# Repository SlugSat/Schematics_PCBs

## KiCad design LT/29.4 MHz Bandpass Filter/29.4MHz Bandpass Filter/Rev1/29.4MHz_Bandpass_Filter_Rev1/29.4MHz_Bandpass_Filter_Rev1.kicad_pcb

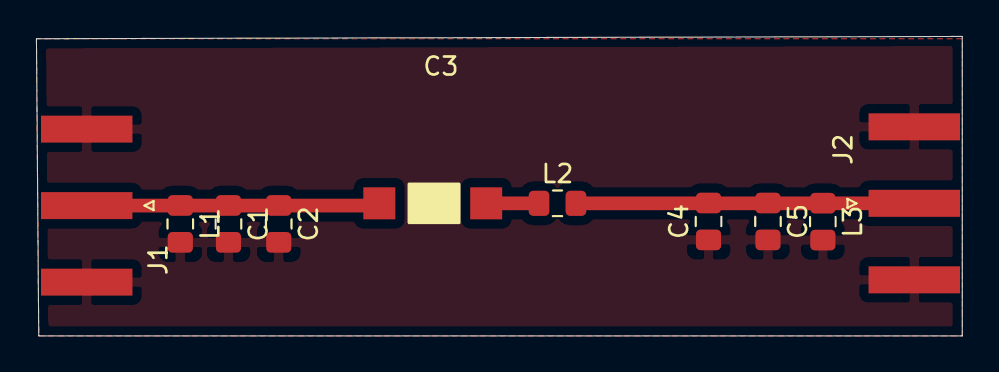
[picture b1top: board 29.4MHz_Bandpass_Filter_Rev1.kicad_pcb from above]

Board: 2 copper layers, 51.4 x 16.6 mm, 10 parts (0 on the bottom side), 4 nets.

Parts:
C1, C2, C4, C5: 1.2nF; C_0805_2012Metric_Pad1.15x1.40mm_HandSolder
C3: C_Variable; Variable Capacitor
J1, J2: Conn_Coaxial; SMA_Amphenol_132289_EdgeMount
L1, L3: 12nH; L_0805_2012Metric_Pad1.15x1.40mm_HandSolder
L2: 5.6uH; L_0805_2012Metric_Pad1.15x1.40mm_HandSolder

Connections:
GND: C1.2, C2.2, C4.1, C5.2, J1.2, J2.2, L1.2, L3.2
unnamed: C1.1, C2.1, C3.2, J1.1, L1.1
unnamed: C3.1, L2.1
unnamed: C4.2, C5.1, J2.1, L2.2, L3.1

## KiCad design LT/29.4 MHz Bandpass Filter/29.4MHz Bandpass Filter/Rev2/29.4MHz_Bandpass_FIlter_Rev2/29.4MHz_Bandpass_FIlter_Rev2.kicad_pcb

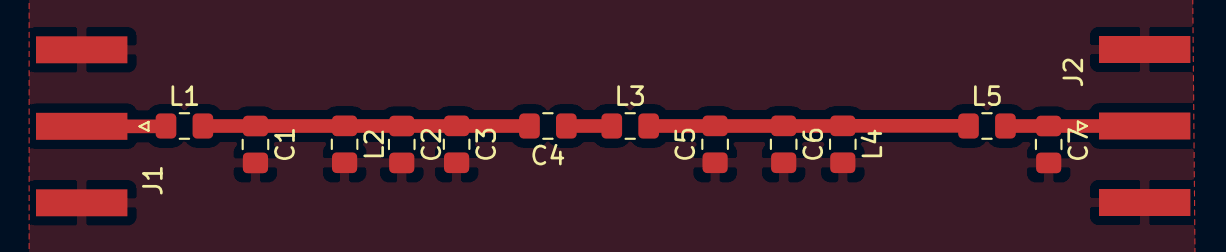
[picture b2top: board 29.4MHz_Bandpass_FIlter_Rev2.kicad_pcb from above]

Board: 2 copper layers, 14 parts (0 on the bottom side), 6 nets.

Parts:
C1, C7: 150pF; C_0805_2012Metric_Pad1.15x1.40mm_HandSolder
C2, C5: 1.5nF; C_0805_2012Metric_Pad1.15x1.40mm_HandSolder
C3, C6: 100pF; C_0805_2012Metric_Pad1.15x1.40mm_HandSolder
C4: 6.2pF; C_0805_2012Metric_Pad1.15x1.40mm_HandSolder
J1, J2: Conn_Coaxial; SMA_Amphenol_132289_EdgeMount
L1, L5: 82nH; L_0805_2012Metric_Pad1.15x1.40mm_HandSolder
L2: 18nH; L_0805_2012Metric_Pad1.15x1.40mm_HandSolder
L3: 4.7uH; L_0805_2012Metric_Pad1.15x1.40mm_HandSolder
L4: L; L_0805_2012Metric_Pad1.15x1.40mm_HandSolder

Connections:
GND: C1.2, C2.2, C3.2, C5.1, C6.2, C7.2, J1.2, J2.2, L2.2, L4.2
unnamed: C1.1, C2.1, C3.1, C4.2, L1.2, L2.1
unnamed: C4.1, L3.1
unnamed: C5.2, C6.1, L3.2, L4.1, L5.1
unnamed: C7.1, J2.1, L5.2
unnamed: J1.1, L1.1

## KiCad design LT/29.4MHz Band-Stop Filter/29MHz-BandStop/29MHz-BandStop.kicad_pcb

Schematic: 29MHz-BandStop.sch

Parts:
C1, C9: 8.2p; C_0805_2012Metric_Pad1.15x1.40mm_HandSolder
C2, C3, C6, C7, C10: C_Variable; CAP_trimmer_SGC3
C4, C8: 1.2n; C_0805_2012Metric_Pad1.15x1.40mm_HandSolder
C5: 15p; C_0805_2012Metric_Pad1.15x1.40mm_HandSolder
J1, J2: Conn_Coaxial; SMA_Molex_73251-1153_EdgeMount_Horizontal
L1, L9: 3.6u; C_0805_2012Metric_Pad1.15x1.40mm_HandSolder
L4, L8: 24n; C_0805_2012Metric_Pad1.15x1.40mm_HandSolder
L5: 2u; C_0805_2012Metric_Pad1.15x1.40mm_HandSolder
U1, U2, U3, U4, U5: LM3-IND; IND_trimmer_7M3

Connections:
GND: J1.2 (Ext), J2.2 (Ext), L1.2, L5.2, L9.2, U1.3, U3.3, U5.3
unnamed: C1.1, C2.1, C3.2, C4.1, J1.1 (In), L4.1, U2.1
unnamed: C1.2, C2.2, L1.1, U1.1
unnamed: C3.1, C4.2, C5.1, C6.1, C7.2, C8.1, L4.2, L8.1, U2.3, U4.1
unnamed: C5.2, C6.2, L5.1, U3.1
unnamed: C7.1, C8.2, C9.1, C10.1, J2.1 (In), L8.2, U4.3
unnamed: C9.2, C10.2, L9.1, U5.1

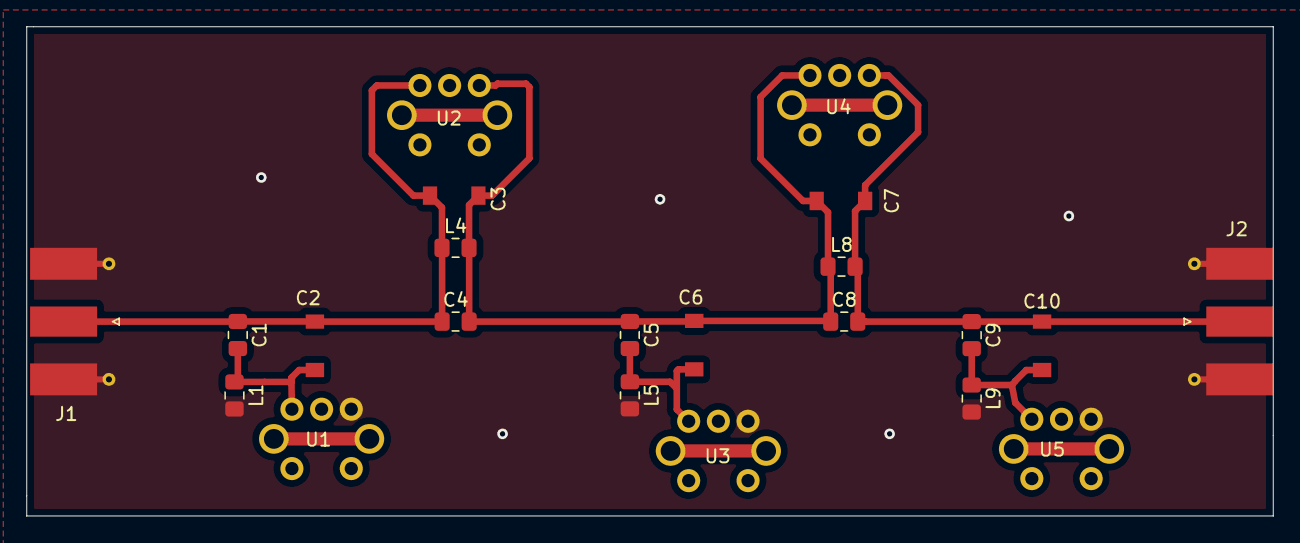
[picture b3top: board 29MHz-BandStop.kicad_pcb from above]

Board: 2 copper layers, 94.5 x 37.1 mm, 22 parts (0 on the bottom side), 7 nets.

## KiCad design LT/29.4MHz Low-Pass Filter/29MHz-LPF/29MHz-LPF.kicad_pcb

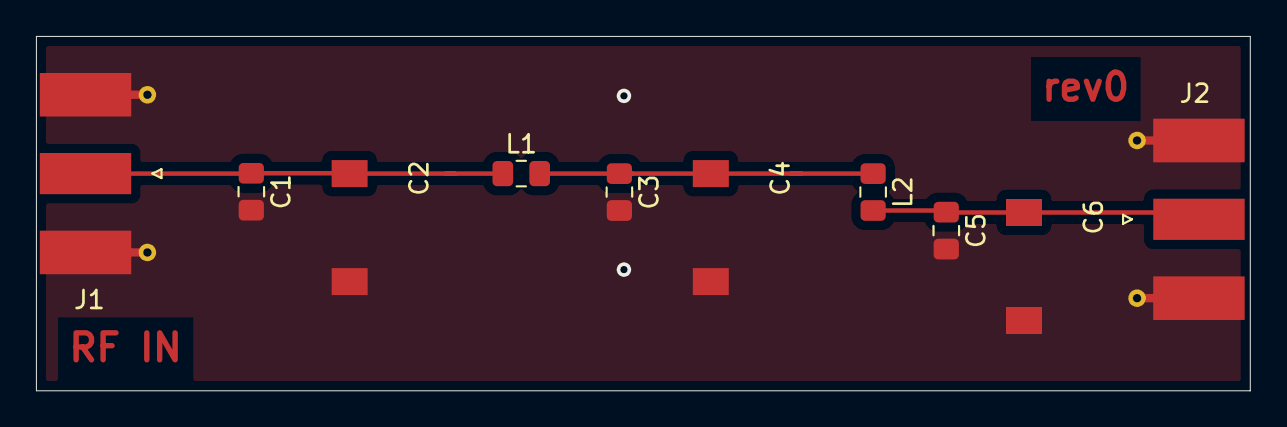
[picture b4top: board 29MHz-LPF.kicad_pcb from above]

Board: 2 copper layers, 67.4 x 19.7 mm, 10 parts (0 on the bottom side), 4 nets.

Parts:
C1, C5: 180p; C_0805_2012Metric_Pad1.15x1.40mm_HandSolder
C2, C4, C6: C_Variable; CAP_Trimmer_TZB4Z
C3: 270p; C_0805_2012Metric_Pad1.15x1.40mm_HandSolder
J1, J2: Conn_Coaxial; SMA_Molex_73251-1153_EdgeMount_Horizontal
L1, L2: 330n; L_0805_2012Metric_Pad1.15x1.40mm_HandSolder

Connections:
GND: C1.2, C2.2, C3.2, C4.2, C5.2, C6.2, J1.2, J2.2
unnamed: C1.1, C2.1, J1.1, L1.1
unnamed: C3.1, C4.1, L1.2, L2.1
unnamed: C5.1, C6.1, J2.1, L2.2

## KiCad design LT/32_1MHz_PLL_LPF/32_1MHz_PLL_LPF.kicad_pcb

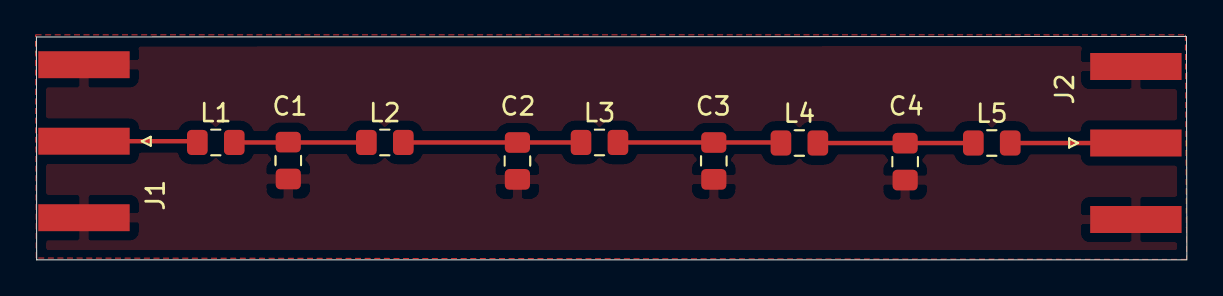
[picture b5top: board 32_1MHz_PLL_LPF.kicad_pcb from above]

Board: 2 copper layers, 63.9 x 12.4 mm, 11 parts (0 on the bottom side), 7 nets.

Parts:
C1, C4: 120pF; C_0805_2012Metric_Pad1.15x1.40mm_HandSolder
C2, C3: 200pF; C_0805_2012Metric_Pad1.15x1.40mm_HandSolder
J1, J2: Conn_Coaxial; SMA_Amphenol_132289_EdgeMount
L1, L5: Matching; L_0805_2012Metric_Pad1.15x1.40mm_HandSolder
L2: 360nH; L_0805_2012Metric_Pad1.15x1.40mm_HandSolder
L3: 390pF; L_0805_2012Metric_Pad1.15x1.40mm_HandSolder
L4: 360pF; L_0805_2012Metric_Pad1.15x1.40mm_HandSolder

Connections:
GND: C1.2, C2.2, C3.2, C4.2, J1.2, J2.2
unnamed: C1.1, L1.2, L2.1
unnamed: C2.1, L2.2, L3.1
unnamed: C3.1, L3.2, L4.1
unnamed: C4.1, L4.2, L5.1
unnamed: J1.1, L1.1
unnamed: J2.1, L5.2

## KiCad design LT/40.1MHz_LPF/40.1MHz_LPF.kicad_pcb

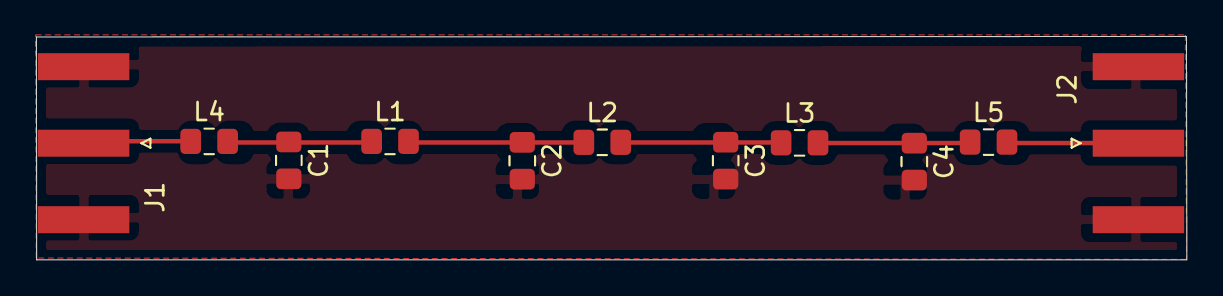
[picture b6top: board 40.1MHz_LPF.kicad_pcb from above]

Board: 2 copper layers, 63.9 x 12.4 mm, 11 parts (0 on the bottom side), 7 nets.

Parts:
C1: 91pF; C_0805_2012Metric_Pad1.15x1.40mm_HandSolder
C2, C3, C4: 160pF; C_0805_2012Metric_Pad1.15x1.40mm_HandSolder
J1, J2: Conn_Coaxial; SMA_Amphenol_132289_EdgeMount
L1, L3: 270nH; L_0805_2012Metric_Pad1.15x1.40mm_HandSolder
L2: 330nH; L_0805_2012Metric_Pad1.15x1.40mm_HandSolder
L4, L5: shorted; L_0805_2012Metric_Pad1.15x1.40mm_HandSolder

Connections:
GND: C1.2, C2.2, C3.2, C4.2, J1.2, J2.2
unnamed: C1.1, L1.1, L4.2
unnamed: C2.1, L1.2, L2.1
unnamed: C3.1, L2.2, L3.1
unnamed: C4.1, L3.2, L5.1
unnamed: J1.1, L4.1
unnamed: J2.1, L5.2

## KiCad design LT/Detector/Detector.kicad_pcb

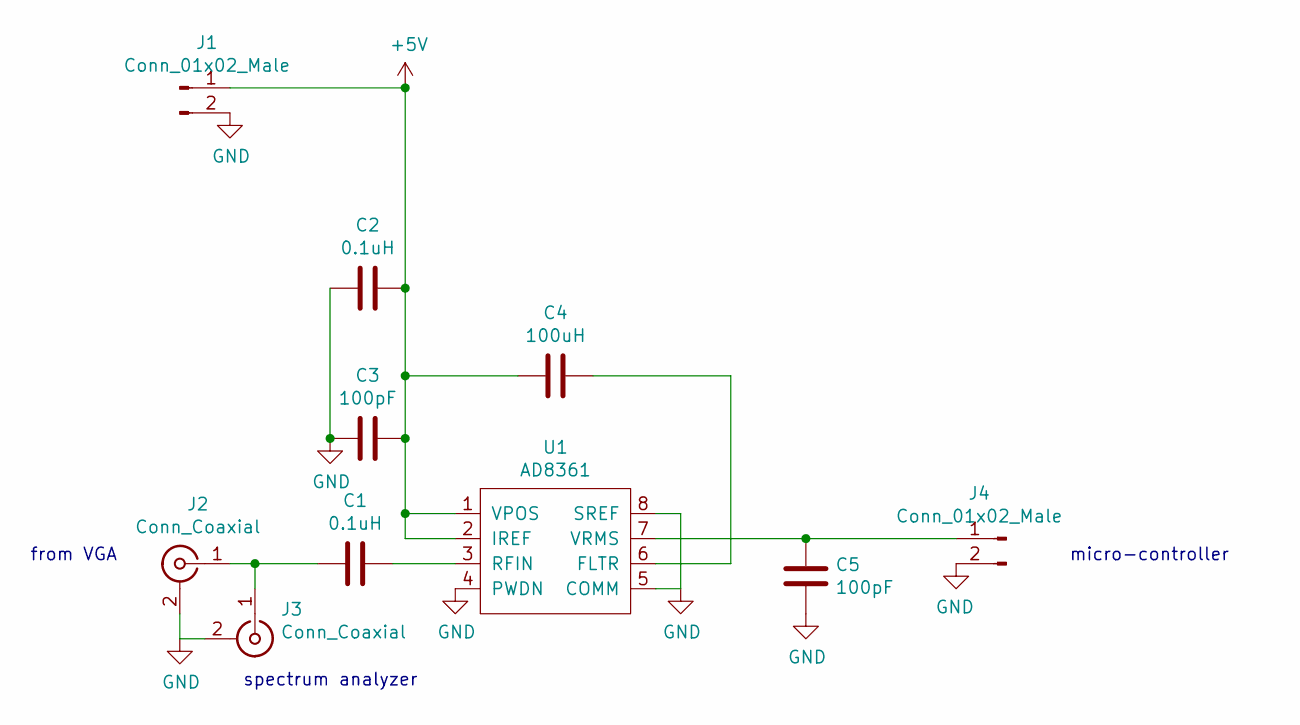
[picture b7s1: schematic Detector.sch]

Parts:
C1, C2: 0.1uH; C_0805_2012Metric_Pad1.15x1.40mm_HandSolder
C3, C5: 100pF; C_0805_2012Metric_Pad1.15x1.40mm_HandSolder
C4: 100uH; C_1206_3216Metric_Pad1.42x1.75mm_HandSolder
J1, J4: Conn_01x02_Male; PinHeader_1x02_P2.54mm_Vertical
J2, J3: Conn_Coaxial; SMA_Amphenol_132289_EdgeMount
U1: AD8361; MSOP-8_3x3mm_P0.65mm

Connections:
+5V: C2.1, C3.1, C4.2, J1.1, U1.1 (VPOS), U1.2 (IREF)
GND: C2.2, C3.2, C5.2, J1.2, J2.2 (Ext), J3.2 (Ext), J4.2, U1.4 (PWDN), U1.5 (COMM), U1.8 (SREF)
unnamed: C1.1, U1.3 (RFIN)
unnamed: C1.2, J2.1 (In), J3.1 (In)
unnamed: C4.1, U1.6 (FLTR)
unnamed: C5.1, J4.1, U1.7 (VRMS)

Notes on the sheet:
from VGA
spectrum analyzer
micro-controller

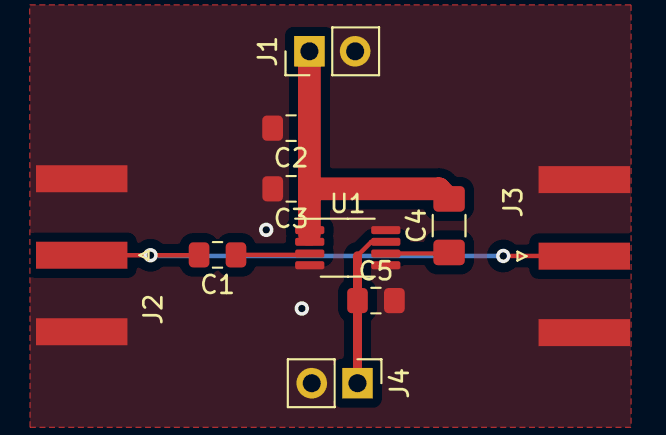
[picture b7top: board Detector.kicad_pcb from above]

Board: 2 copper layers, 10 parts (0 on the bottom side), 6 nets.

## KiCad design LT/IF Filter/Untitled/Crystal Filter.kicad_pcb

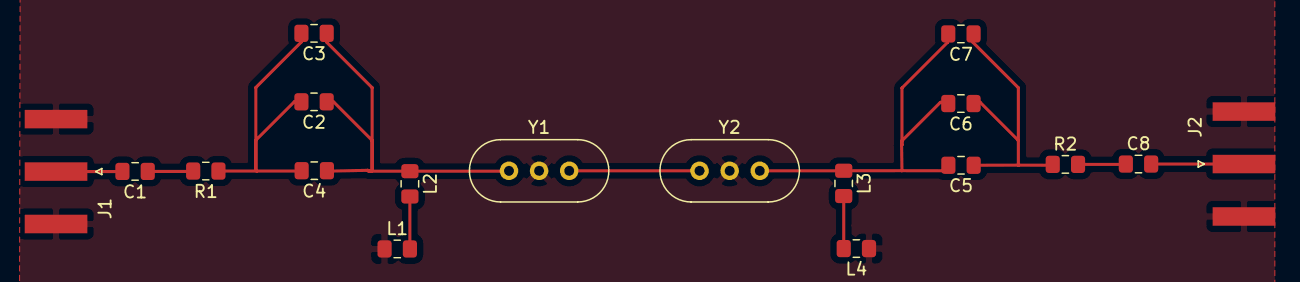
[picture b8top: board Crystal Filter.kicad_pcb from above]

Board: 2 copper layers, 18 parts (0 on the bottom side), 12 nets.

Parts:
C1, C2, C3, C4, C5, C6, C7, C8: C; C_0805_2012Metric_Pad1.15x1.40mm_HandSolder
J1, J2: Conn_Coaxial; SMA_Amphenol_132289_EdgeMount
L1, L2, L3, L4: L; L_0805_2012Metric_Pad1.15x1.40mm_HandSolder
R1, R2: 0; R_0805_2012Metric_Pad1.15x1.40mm_HandSolder
Y1, Y2: Crystal; Crystal_HC49-U-3Pin_Vertical

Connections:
GND: J1.2, J2.2, L1.1, L4.1, Y1.2, Y2.2
unnamed: C1.1, R1.2
unnamed: C1.2, J1.1
unnamed: C2.1, C3.1, C4.1, L2.1, Y1.1
unnamed: C2.2, C3.2, C4.2, R1.1
unnamed: C5.1, C6.1, C7.1, R2.1
unnamed: C5.2, C6.2, C7.2, L3.1, Y2.3
unnamed: C8.1, R2.2
unnamed: C8.2, J2.1
unnamed: L1.2, L2.2
unnamed: L3.2, L4.2
unnamed: Y1.3, Y2.1
